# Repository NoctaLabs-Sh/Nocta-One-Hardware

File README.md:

# Nocta Hardware

Open hardware for the Nocta vault: an offline password and credential manager
with a 2.7 inch e-ink screen, optional Bluetooth LE, and no cloud service
behind it.

This repository is the design, not a product. The device is a prototype, it is
not for sale, and there is no ship date.

Built by [Nocta Labs](https://noctalabs.sh), Leuven, Belgium.

## What is in here

| Path | What it is |
| --- | --- |
| `Hardware/OpenVault.kicad_sch` | Schematic, KiCad |
| `Hardware/Schematic.pdf` | The same schematic, readable without KiCad |
| `Hardware/OpenVault.kicad_pcb` | Board layout, KiCad |
| `Hardware/production/` | Fabrication packages: gerbers, positions, BOMs |
| `Hardware/3D/` | STEP models for individual component packages |
| `Hardware/Datasheets/` | Datasheets for the parts used |
| `Hardware/Footprints/`, `Symbols/` | Project libraries |

## What is not in here yet

- **Firmware.** Still being written. It will be published when it is worth
  reading, and the licence for it is not decided.
- **The enclosure.** No named enclosure model is published yet.
- **Photographs.** Coming with the next write-up.

## Licence

[CERN Open Hardware Licence Version 2, Strongly Reciprocal](LICENSE)
(`CERN-OHL-S-2.0`). Strongly reciprocal means anything you make from this and
distribute has to stay open under the same terms. That is deliberate.

## Reading the files

Open `Hardware/OpenVault.kicad_pro` in KiCad 8 or later, or start with
`Hardware/Schematic.pdf` if you just want to read it. The fabrication packages
under `Hardware/production/` are what actually went to the board house.

## Use of AI

AI assistance, primarily Anthropic's Claude, is used in the development of this
hardware.

Its role is limited to review and analysis: reading datasheets and verifying pin
assignments and component values against them, reviewing the schematic and the
board layout, triaging ERC and DRC output, maintaining helper scripts, and
drafting documentation.

Component selection, the board stackup, the USB differential pair impedance and
all security related decisions are made by the maintainers. No AI system commits
to this repository, and every change is reviewed by a maintainer before it
reaches `main`.

No part of this design has been validated by an AI system, and maintainer review
does not amount to electrical or security qualification. The design should be
read against the component datasheets and verified independently before
fabrication or use. The warranty and liability disclaimers in the licence apply
in full.

Contributions developed with AI assistance are accepted, provided the use is
disclosed in the pull request and the contributor can account for the work
submitted.

## Telling us we are wrong

Open an issue. A mistake found in the schematic now is worth more to us than
a compliment later :)

For anything sensitive, mail hello@noctalabs.sh first and we will credit you
publicly once it is fixed.

## Related

- [noctalabs.sh](https://noctalabs.sh) and its [security page](https://noctalabs.sh/security)
- [The blog](https://noctalabs.sh/blog), where revisions get written up

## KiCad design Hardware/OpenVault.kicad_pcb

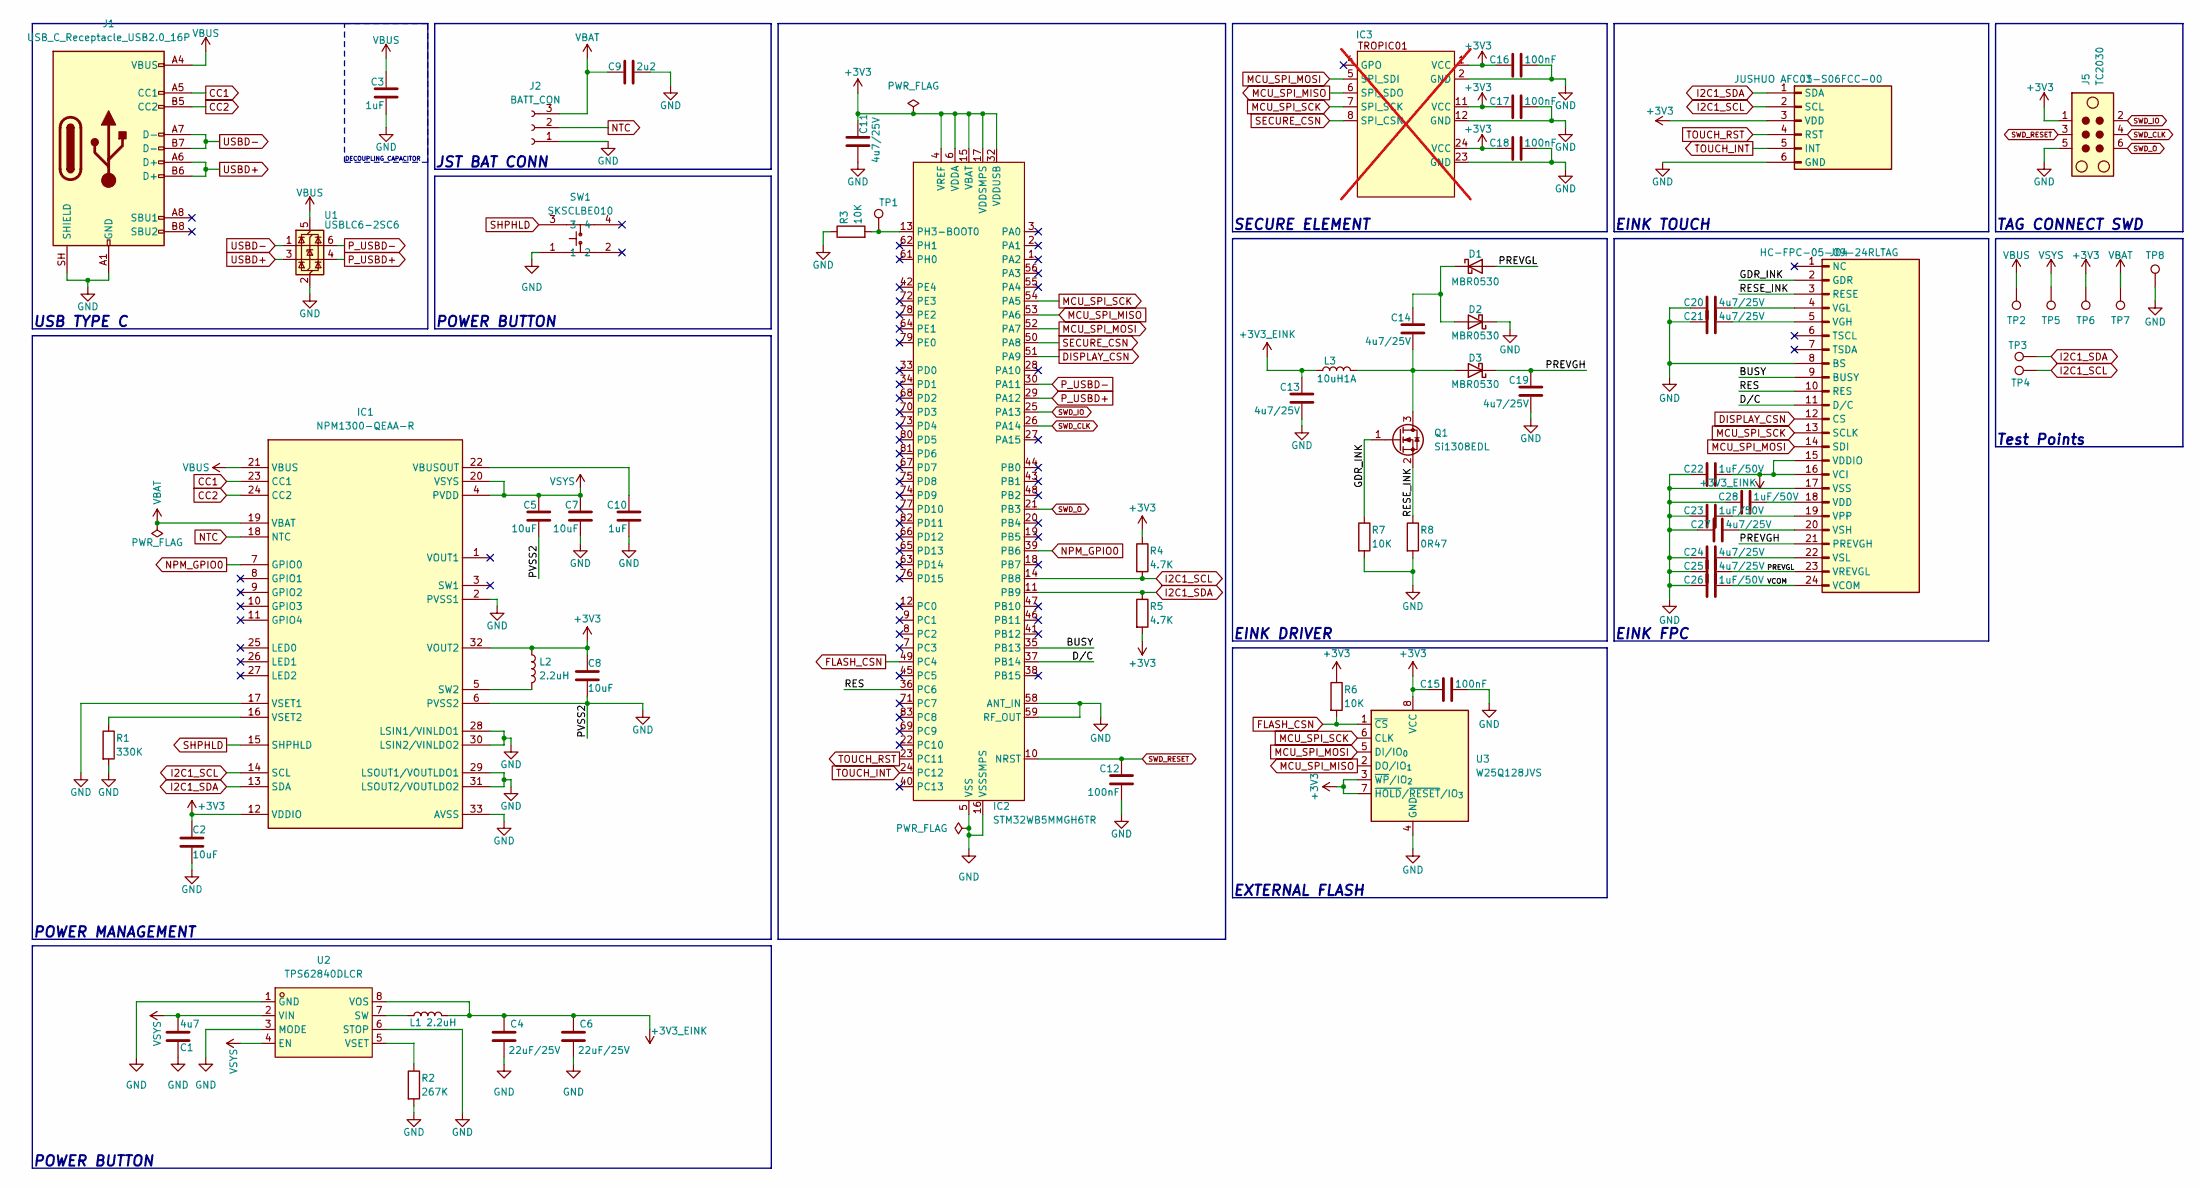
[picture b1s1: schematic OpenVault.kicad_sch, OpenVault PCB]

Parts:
C1: 4u7; C_0805_2012Metric; LCSC C1779
C2, C5, C7, C8: 10uF; C_0603_1608Metric; LCSC C19702
C3, C10: 1uF; C_0402_1005Metric; LCSC C52923
C4, C6: 22uF/25V; C_0805_2012Metric; LCSC C45783
C9: 2u2; C_0603_1608Metric; LCSC C23630
C11, C13, C14, C19, C20, C21, C24, C25, C27: 4u7/25V; C_0805_2012Metric; LCSC C1779
C12, C15, C16, C17, C18: 100nF; C_0402_1005Metric; LCSC C1525
C22, C23, C26, C28: 1uF/50V; C_0603_1608Metric; LCSC C15849
D1, D2, D3: MBR0530; D_SOD-123; LCSC C77336
IC1: NPM1300-QEAA-R; QFN-32-1EP_5x5mm_P0.5mm_EP3.45x3.45mm_ThermalVias; Manufacturer_Part_Number NPM1300-QEAA-R7; Mouser Part Number 949-NPM1300-QEAA-R7
IC2: STM32WB5MMGH6TR; ST-SiP-LGA-86-11x7.3mm; LCSC C5184586
IC3: TROPIC01; QFN-32-1EP_4x4mm_P0.4mm_EP2.9x2.9mm; not fitted
J1: USB_C_Receptacle_USB2.0_16P; USB_C_Receptacle_GCT_USB4105-xx-A_16P_TopMnt_Horizontal; LCSC C2765186
J2: BATT_CON; JST_SH_SM03B-SRSS-TB_1x03-1MP_P1.00mm_Horizontal; LCSC C160403
J3: JUSHUO AFC01-S06FCC-00; FPC-SMD_AFC01-S06FCC-00; LCSC C262262
J04: HC-FPC-05-09-24RLTAG; FPC-SMD_24P-P0.50_HC-FPC-05-09-24RLTAG; LCSC C5213757
J5: TC2030; Tag-Connect_TC2030-IDC-NL_2x03_P1.27mm_Vertical
L1, L2: 2.2uH; IND-SMD_L2.0-W1.6; LCSC C71386
L3: 10uH1A; L_Sunlord_SWPA4030S; LCSC C497803
Q1: Si1308EDL; SOT-323_SC-70; LCSC C7603347
R1: 330K; R_0603_1608Metric; LCSC C23137
R2: 267K; R_0402_1005Metric; LCSC C270622
R3, R6, R7: 10K; R_0603_1608Metric; LCSC C25804
R4, R5: 4.7K; R_0603_1608Metric; LCSC C23162
R8: 0R47; R_0603_1608Metric; LCSC C23411
SW1: SKSCLBE010; KEY-SMD_4P-SKSCLXX010; LCSC C115361
TP1, TP2, TP3, TP4, TP5, TP6, TP7, TP8: TestPoint; TestPoint_Pad_D1.0mm
U1: USBLC6-2SC6; SOT-23-6; LCSC C2687116
U2: TPS62840DLCR; VSON-8_L2.0-W1.5-P0.50-BL; LCSC Part C2071859
U3: W25Q128JVS; SOIC-8_5.3x5.3mm_P1.27mm; LCSC C97521

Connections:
+3V3: C2.2, C8.2, C11.1, C15.1, C16.1, C17.1, C18.1, IC1.12 (VDDIO), IC1.32 (VOUT2), IC2.4 (VREF), IC2.6 (VDDA), IC2.15 (VBAT), IC2.17 (VDDSMPS), IC2.32 (VDDUSB), IC3.1 (VCC), IC3.11 (VCC), IC3.24 (VCC), J3.3 (VDD), J5.1, L2.1, R4.1, R5.2, R6.1, TP6.1 (1_1), U3.3 (~WP/IO_{2}), U3.7 (~HOLD/~RESET/IO_{3}), U3.8 (VCC)
+3V3_EINK: C4.1, C6.1, C13.1, C22.2, J04.15 (VDDIO), J04.16 (VCI), L1.2, L3.1, U2.8 (VOS)
/BUSY: IC2.35 (PB13), J04.9 (BUSY)
/D/C: IC2.37 (PB14), J04.11 (D/C)
/GDR_INK: J04.2 (GDR), Q1.1 (G), R7.1
/PREVGH: C19.1, D3.1 (K), J04.21 (PREVGH)
/PREVGL: C25.2, D1.2 (A), J04.23 (VREVGL)
/RES: IC2.36 (PC6), J04.10 (RES)
/RESE_INK: J04.3 (RESE), Q1.2 (S), R8.1
/VCOM: C26.2, J04.24 (VCOM)
CC1: IC1.23 (CC1), J1.A5 (CC1)
CC2: IC1.24 (CC2), J1.B5 (CC2)
DISPLAY_CSN: IC2.51 (PA9), J04.12 (CS)
FLASH_CSN: IC2.49 (PC4), R6.2, U3.1 (~CS)
GND: C1.1, C2.1, C3.2, C4.2, C5.2, C6.2, C7.2, C8.1, C9.2, C10.2, C11.2, C12.2, C13.2, C15.2, C16.2, C17.2, C18.2, C19.2, C20.1, C21.1, C22.1, C23.1, C24.1, C25.1, C26.1, C27.1, C28.1, D2.1 (K), IC1.2 (PVSS1), IC1.6 (PVSS2), IC1.17 (VSET1), IC1.28 (LSIN1/VINLDO1), IC1.29 (LSOUT1/VOUTLDO1), IC1.30 (LSIN2/VINLDO2), IC1.31 (LSOUT2/VOUTLDO2), IC1.33 (AVSS), IC2.5 (VSS), IC2.16 (VSSSMPS), IC2.31 (VSS), IC2.57 (VSS), IC2.58 (ANT_IN), IC2.59 (RF_OUT), IC2.60 (VSS), IC2.84 (VSS), IC2.86 (VSS), IC3.2 (GND), IC3.12 (GND), IC3.23 (GND), J1.A1 (GND), J1.A12 (GND), J1.B1 (GND), J1.B12 (GND), J1.SH (SHIELD), J2.1, J3.6 (GND), J04.8 (BS), J04.17 (VSS), J5.5, R1.2, R2.2, R3.1, R7.2, R8.2, SW1.1, TP8.1 (1_1), U1.2 (GND), U2.1 (GND), U2.3 (MODE), U2.6 (STOP), U3.4 (GND)
I2C1_SCL: IC1.14 (SCL), IC2.14 (PB8), J3.2 (SCL), R4.2, TP4.1
I2C1_SDA: IC1.13 (SDA), IC2.11 (PB9), J3.1 (SDA), R5.1, TP3.1
MCU_SPI_MISO: IC2.53 (PA6), IC3.6 (SPI_SDO), U3.2 (DO/IO_{1})
MCU_SPI_MOSI: IC2.52 (PA7), IC3.5 (SPI_SDI), J04.14 (SDI), U3.5 (DI/IO_{0})
MCU_SPI_SCK: IC2.54 (PA5), IC3.7 (SPI_SCK), J04.13 (SCLK), U3.6 (CLK)
NPM_GPIO0: IC1.7 (GPIO0), IC2.39 (PB6)
NTC: IC1.18 (NTC), J2.2
unnamed: C14.1, D1.1 (K), D2.2 (A)
unnamed: C14.2, D3.2 (A), L3.2, Q1.3 (D)
unnamed: IC1.5 (SW2), L2.2
unnamed: C10.1, IC1.22 (VBUSOUT)
unnamed: IC1.16 (VSET2), R1.1
unnamed: IC2.13 (PH3-BOOT0), R3.2, TP1.1 (1_1)
unnamed: C28.2, J04.18 (VDD)
unnamed: C21.2, J04.5 (VGH)
unnamed: C20.2, J04.4 (VGL)
unnamed: C23.2, J04.19 (VPP)
unnamed: C27.2, J04.20 (VSH)
unnamed: C24.2, J04.22 (VSL)
unnamed: L1.1, U2.7 (SW)
unnamed: R2.1, U2.5 (VSET)
P_USBD+: IC2.29 (PA12), U1.4 (I/O2)
P_USBD-: IC2.30 (PA11), U1.6 (I/O1)
SECURE_CSN: IC2.50 (PA8), IC3.8 (SPI_CSN)
SHPHLD: IC1.15 (SHPHLD), SW1.3
SWD_CLK: IC2.26 (PA14), J5.4
SWD_IO: IC2.25 (PA13), J5.2
SWD_O: IC2.21 (PB3), J5.6
SWD_RESET: C12.1, IC2.10 (NRST), J5.3
TOUCH_INT: IC2.24 (PC12), J3.5 (INT)
TOUCH_RST: IC2.23 (PC11), J3.4 (RST)
USBD+: J1.A6 (D+), J1.B6 (D+), U1.3 (I/O2)
USBD-: J1.A7 (D-), J1.B7 (D-), U1.1 (I/O1)
VBAT: C9.1, IC1.19 (VBAT), J2.3, TP7.1 (1_1)
VBUS: C3.1, IC1.21 (VBUS), J1.A4 (VBUS), J1.A9 (VBUS), J1.B4 (VBUS), J1.B9 (VBUS), TP2.1 (1_1), U1.5 (VBUS)
VSYS: C1.2, C5.1, C7.1, IC1.4 (PVDD), IC1.20 (VSYS), TP5.1 (1_1), U2.2 (VIN), U2.4 (EN)

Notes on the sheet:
TAG CONNECT SWD
DECOUPLING CAPACITOR
JST BAT CONN
EINK DRIVER
Test Points
EXTERNAL FLASH
POWER BUTTON
USB TYPE C
EINK FPC
POWER MANAGEMENT
SECURE ELEMENT
EINK TOUCH

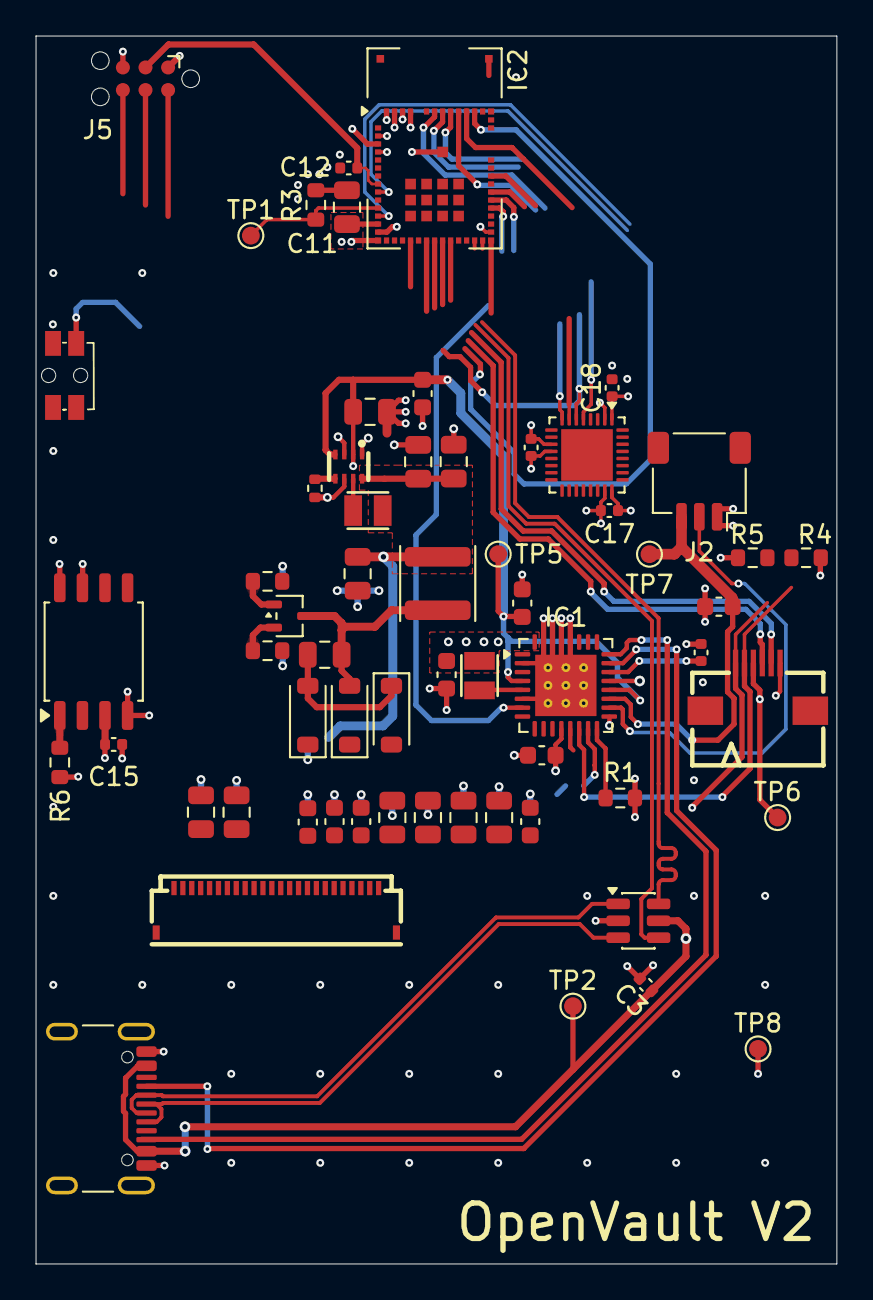
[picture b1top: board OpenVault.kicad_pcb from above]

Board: 4 copper layers, 45.0 x 69.0 mm, 61 parts (0 on the bottom side), 51 nets.

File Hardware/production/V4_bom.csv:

Designator,Footprint,Quantity,Value,LCSC Part #
C1,0805,1,4u7,C1779
"C10, C3",0402,2,1uF,C52923
"C11, C13, C14, C19, C20, C21, C24, C25, C27",0805,9,4u7/25V,C1779
"C12, C15, C16, C17, C18",0402,5,100nF,C1525
"C2, C5, C7, C8",0603,4,10uF,C19702
"C22, C23, C26, C28",0603,4,1uF/50V,C15849
"C4, C6",0805,2,22uF/25V,C45783
C9,0603,1,2u2,C23630
"D1, D2, D3",D_SOD-123,3,MBR0530,C77336
IC1,QFN-32-1EP_5x5mm_P0.5mm_EP3.45x3.45mm_ThermalVias,1,NPM1300-QEAA-R,C7466043
IC2,ST-SiP-LGA-86-11x7.3mm,1,STM32WB5MMGH6TR,C5184586
J04,FPC-SMD_24P-P0.50_HC-FPC-05-09-24RLTAG,1,HC-FPC-05-09-24RLTAG,C5213757
J1,USB_C_Receptacle_GCT_USB4105-xx-A_16P_TopMnt_Horizontal,1,USB_C_Receptacle_USB2.0_16P,C2765186
J2,JST_SH_SM03B-SRSS-TB_1x03-1MP_P1.00mm_Horizontal,1,BATT_CON,C160403
J3,FPC-SMD_AFC01-S06FCC-00,1,JUSHUO AFC01-S06FCC-00,C262262
"L1, L2",IND-SMD_L2.0-W1.6,2,2.2uH,C71386 
L3,L_Sunlord_SWPA4030S,1,10uH1A,C497803
Q1,SOT-323_SC-70,1,Si1308EDL,C7603347
R1,0603,1,330K,C23137
R2,0402,1,267K,C270622 
"R3, R6, R7",0603,3,10K,C25804 
"R4, R5",0603,2,4.7K,C23162
R8,0603,1,0R47,C23411
SW1,KEY-SMD_4P-SKSCLXX010,1,SKSCLBE010,C115361
U1,SOT-23-6,1,USBLC6-2SC6,C2687116
U2,VSON-8_L2.0-W1.5-P0.50-BL,1,TPS62840DLCR,C2071859
U3,SOIC-8_5.3x5.3mm_P1.27mm,1,W25Q128JVS,C97521

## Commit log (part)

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2026-03-23 Working working
2026-03-23 tag connect
2026-03-23 all parts placed
2026-04-04 lot of work
2026-04-26 some hardware chagnes
2026-04-28 final before v2
